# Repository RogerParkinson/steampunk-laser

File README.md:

# steampunk-laser
Plays a noise on ATTiny85 using tone() PWM pin 4 and flashes a couple of LEDs

This code was loaded into an ATTiny85 that was embedded into a toy pistol with a laser pointer in the tip. When the trigger is pulled the tone sounds and the laser is turned on. There are a couple of blinking LEDs as well.

The finished laser looks like this:

[video](https://youtu.be/AGKMF4kWh64)

The handle was designed in blender and 3D printed with a spacein it to hold a LIPO battery.
This is the bare handle:

And this is the handle after painting and covering with fake mother of pearl.

[video](https://youtu.be/AGKMF4kWh64)

We adapted the idea to make a bird scarer with glowing eyes. Some minor changes to the circuit and the code and it wakes up every 15 minutes to scare swallows that were nesting on the side of a house. The noise was adjusted to sound like a growling animal. THis was powered by 2xAA batteries.
This was, in fact, a total failure. The swallows were initially bothers but in 3 weeks they had built a nest on top of it. The batteries were still going well, attesting to the usefulness of the ATTiny85's sleep function.

The circuit for this is shown here:

# Building the Software

We used Arduino IDE 1.6.7 with the [arduino-tiny core](https://code.google.com/archive/p/arduino-tiny/). The arduino-tiny-core is necessary for building ATTiny projects.
The Arduino IDE includes a Boards Manager which will install a core for ATTiny boards but this does *not* include the tone function. The code here will build fine under that core
but you will not hear anything from the speaker. However the arduino-tiny-core does not install automatically, you need do download it and unzip. See the readme file in the unzip. 
But even with that we had to edit the platform.txt file to point to the compiler and we had to move the empty85at*.hex files from ~/Arduino/hardware/tiny/avr/bootloader/empty to ~/Arduino/hardware/tiny/avr/bootloader.

To run the build in the IDE you need to pick the *ATtiny85 @ 1 MHz  (internal oscillator; BOD disabled)* board and then run the compile.

To load it into your board you need an [AVR programmer](https://www.sparkfun.com/products/11801).

# Hardware

This is the parts list for the electronics:
DIP
ATTiny85
Diode
Test button
battery
laser
Speaker
the other parts are either easy to find or up to you to chose what you like, eg the trigger we used is a push button that fitted into the handle.

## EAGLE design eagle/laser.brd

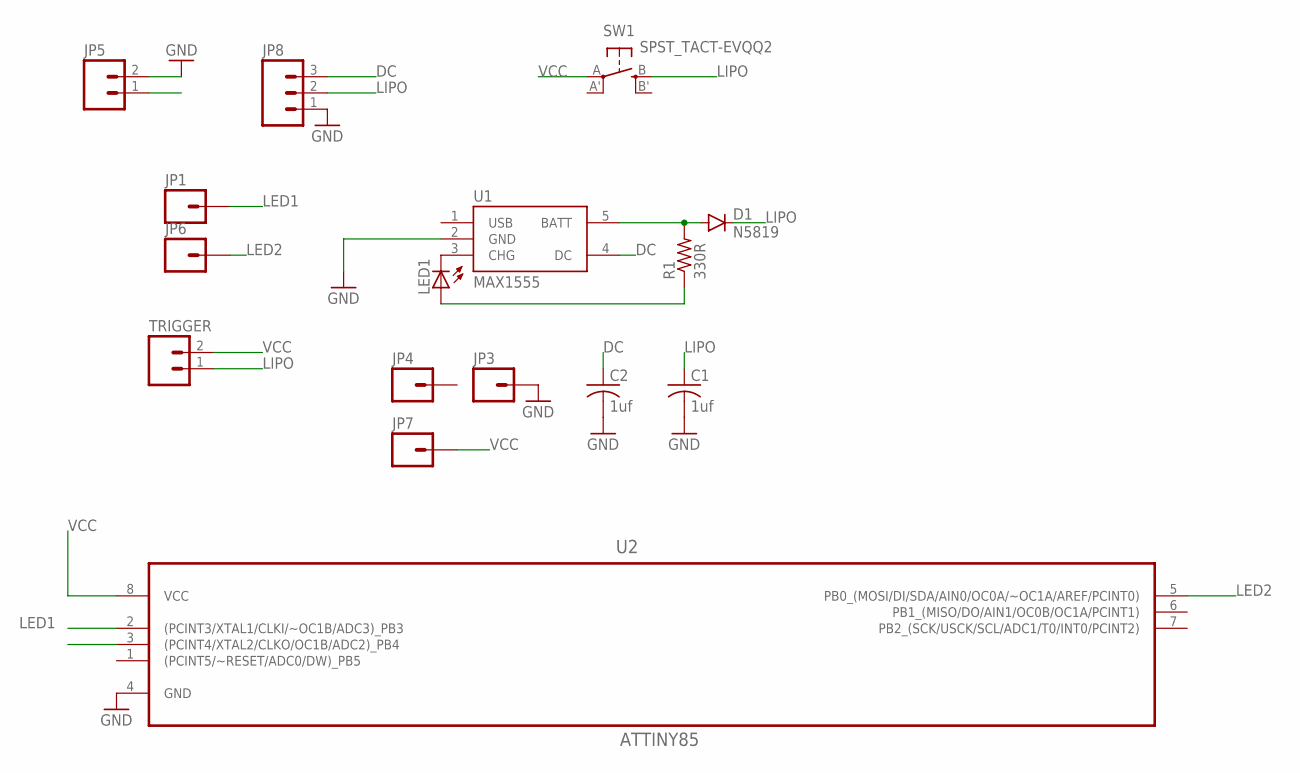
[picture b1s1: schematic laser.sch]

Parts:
C1, C2: 1uf; C0805K
D1: N5819; DIODE-1N4148
JP1, JP3, JP4, JP6, JP7: M01PTH; 1X01
JP5: M02LOCK; 1X02_LOCK
JP8: M03LOCK; 1X03_LOCK
LED1: LEDCHIP-LED0805; CHIP-LED0805
R1: 330R; M0805
SW1: SPST_TACT-EVQQ2; EVQ-Q2
TRIGGER: M02PTH; 1X02
U1: MAX1555; SOT23-5
U2: ATTINY85; DIP254P762X533-8

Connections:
DC: C2.1, JP8.3, U1.4 (DC)
GND: C1.2, C2.2, JP3.1, JP5.2, JP8.1, U1.2 (GND), U2.4 (GND)
LED1: JP1.1, U2.2 ((PCINT3/XTAL1/CLKI/~OC1B/ADC3)_PB3)
LED2: JP6.1, U2.5 (PB0_(MOSI/DI/SDA/AIN0/OC0A/~OC1A/AREF/P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)
LIPO: C1.1, D1.C, JP8.2, SW1.B (S), TRIGGER.1
unnamed: LED1.C, U1.3 (CHG)
unnamed: D1.A, R1.2, U1.5 (BATT)
unnamed: LED1.A, R1.1
TONE: JP5.1, U2.3 ((PCINT4/XTAL2/CLKO/OC1B/ADC2)_PB4)
VCC: JP7.1, SW1.A, TRIGGER.2, U2.8 (VCC)

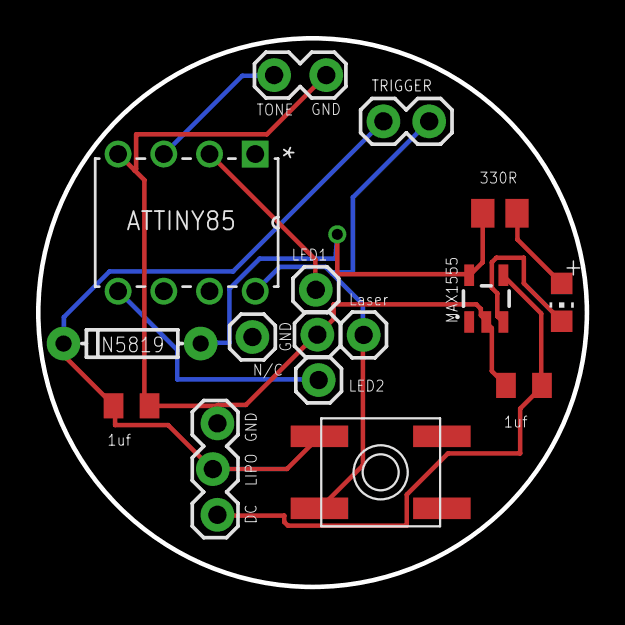
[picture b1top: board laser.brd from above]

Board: 2 copper layers, 30.5 x 30.5 mm, 16 parts (0 on the bottom side), 10 nets.

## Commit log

2012-08-02 Initial directory structure.
2012-08-02 Initial version, though this is all working
2012-09-24 Not sure how it worked with the wrong setting but this one looks better
2013-06-18 Minor library config changes
2015-03-15 Migrating wiki contents from Google Code
2016-05-29 Reworked project to include FakeRat as well as Laser Also moved it to use Arduino IDE rather than Eclipse (Eclipse is too complicated to sustain)
2016-05-29 trying to get video embedded into readme
2017-07-08 Added eagle files and updated description and code

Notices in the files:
eagle/laser.brd:
(c) 2017 R J Parkinson
parts and their libraries:
SparkFun-PowerIC: Licensing: Creative Commons ShareAlike 4.0 International - https://creativecommons.org/licenses/by-sa/4.0
